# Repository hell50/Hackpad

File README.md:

# Rhythm!Pad
yes indeed it go brrr for rhythm games

**This will be documented in the following way:**

Version # or name: \
|\
|- CAD files\
|- QMKs (labeled)\
|- Gerbers

Uhh idk what else to add to the readme

Made with <3 I guess :)

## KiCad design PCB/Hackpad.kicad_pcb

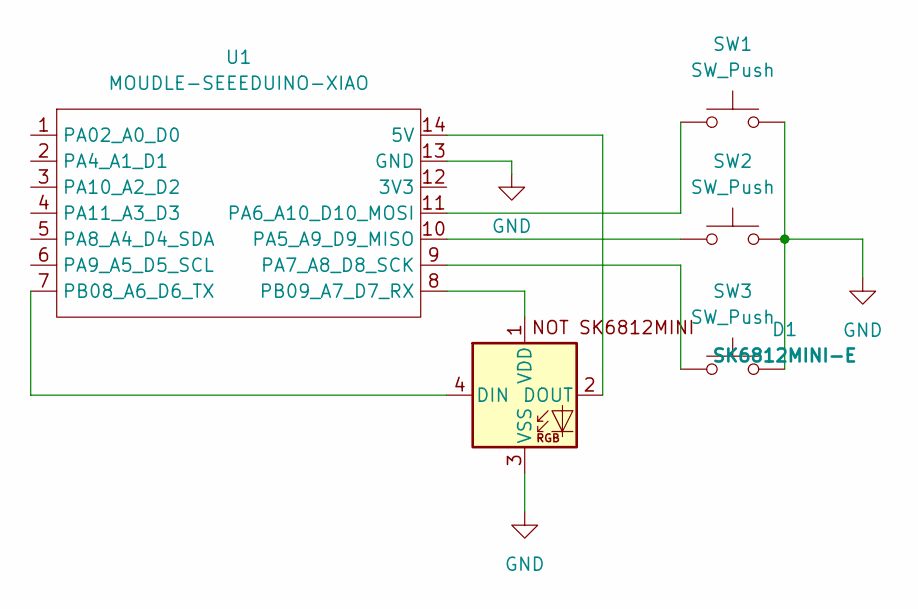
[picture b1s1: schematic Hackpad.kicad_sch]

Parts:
D1: SK6812MINI-E; SK6812MINI-E_fixed
SW1, SW2, SW3: SW_Push; SW_Cherry_MX_1.00u_PCB
U1: MOUDLE-SEEEDUINO-XIAO; XIAO-Generic-Hybrid-14P-2.54-21X17.8MM

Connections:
GND: D1.3 (VSS), SW1.2, SW2.2, SW3.2, U1.13 (GND)
unnamed: D1.4 (DIN), U1.7 (PB08_A6_D6_TX)
unnamed: D1.2 (DOUT), U1.14 (5V)
unnamed: D1.1 (VDD), U1.8 (PB09_A7_D7_RX)
unnamed: SW2.1, U1.10 (PA5_A9_D9_MISO)
unnamed: SW1.1, U1.11 (PA6_A10_D10_MOSI)
unnamed: SW3.1, U1.9 (PA7_A8_D8_SCK)

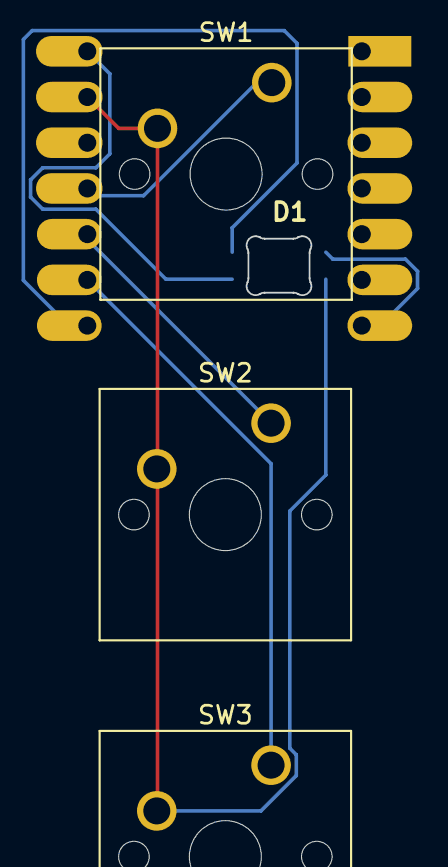
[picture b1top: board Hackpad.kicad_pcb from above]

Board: 2 copper layers, 5 parts (1 on the bottom side), 7 nets.

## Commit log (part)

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2026-03-01 Upload KiCad files
2026-03-01 Upload 3d model file
2026-03-01 Hackpad Firmware
2026-03-01 Rename Hackpad.kicad_pcb to PCB/Hackpad.kicad_pcb
2026-03-01 Rename Hackpad.kicad_pro to PCB/Hackpad.kicad_pro
2026-03-01 Rename Hackpad.kicad_sch to PCB/Hackpad.kicad_sch
2026-03-01 Rename macropad-3key-music.json to Firmware/macropad-3key-music.json
2026-03-01 Add placeholder file for cad folder
